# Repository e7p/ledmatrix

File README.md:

ledmatrix
=========

We got a couple of LED matrices in our Hackerspace /dev/tal in Wuppertal. Here there is held code and other useful things for them.

Important info: The Fusebit for "JTAG" MUST be deactivated for usage of PORT C, which is used by default for serial data!

How to build
------------

To build the Firmware, just enter the directory "main" and type `make`. For flashing the firmware `make flash` can be used, or the main.hex file can be flashed using an arbitrary AVR flashing tool.

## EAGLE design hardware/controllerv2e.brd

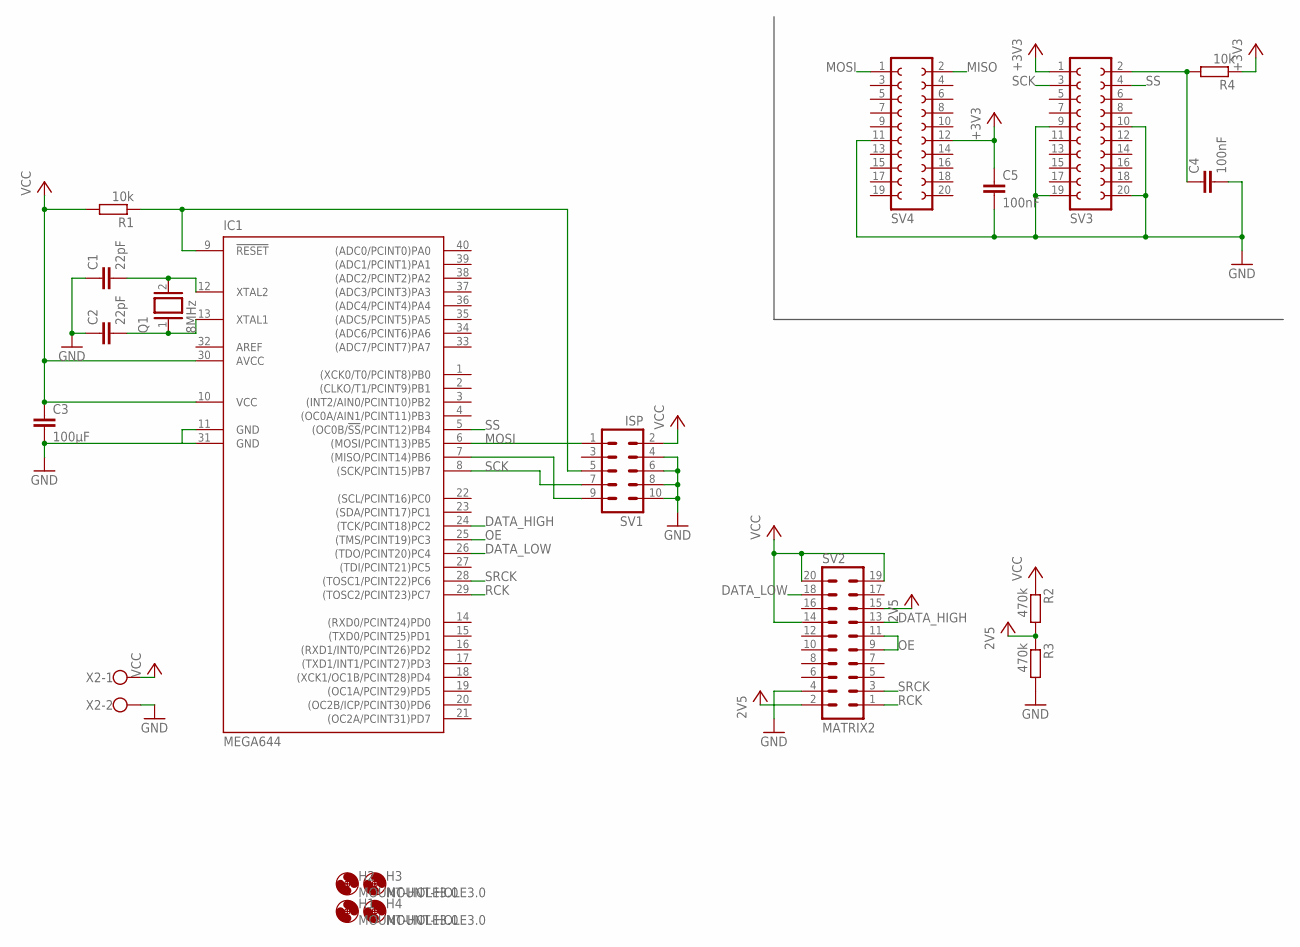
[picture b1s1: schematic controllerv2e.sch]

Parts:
C1, C2: 22pF; C050-024X044
C3: 100µF; C050-030X075
C4, C5: 100nF; C050-024X044
H1, H2, H3, H4: MOUNT-HOLE3.0; 3,0
IC1: MEGA644; DIL40
Q1: 8MHz; QS
R1, R4: 10k; 0207/10
R2, R3: 470k; 0207/10
SV1: ISP; ML10
SV2: MATRIX2; ML20
SV3, SV4: FE10-2
X2: GND; W237-102

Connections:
+3V3: C5.1, R2.2, R3.1, R4.1, SV2.2, SV2.15, SV3.1, SV4.12
AREF: IC1.32 (AREF)
DATA_HIGH: IC1.24 ((TCK/PCINT18)PC2), SV2.13
DATA_LOW: IC1.26 ((TDO/PCINT20)PC4), SV2.18
GND: C1.1, C2.1, C3.2, C4.2, C5.2, IC1.11 (GND), IC1.31 (GND), R3.2, SV1.4, SV1.6, SV1.8, SV1.10, SV2.4, SV3.9, SV3.10, SV3.19, SV3.20, SV4.11, X2.2
MISO: SV4.2
MOSI: IC1.6 ((MOSI/PCINT13)PB5), SV1.1, SV4.1
unnamed: C4.1, R4.2, SV3.2
unnamed: C2.2, IC1.13 (XTAL1), Q1.1
unnamed: C1.2, IC1.12 (XTAL2), Q1.2
unnamed: IC1.9 (!RESET), R1.1, SV1.5
unnamed: IC1.7 ((MISO/PCINT14)PB6), SV1.9
OE: IC1.25 ((TMS/PCINT19)PC3), SV2.9, SV2.11
RCK: IC1.29 ((TOSC2/PCINT23)PC7), SV2.1
SCK: IC1.8 ((SCK/PCINT15)PB7), SV1.7, SV3.3
SRCK: IC1.28 ((TOSC1/PCINT22)PC6), SV2.3
SS: IC1.5 ((OC0B/!SS!/PCINT12)PB4), SV3.4
VCC: C3.1, IC1.10 (VCC), IC1.30 (AVCC), R1.2, R2.1, SV1.2, SV2.14, SV2.19, SV2.20, X2.1

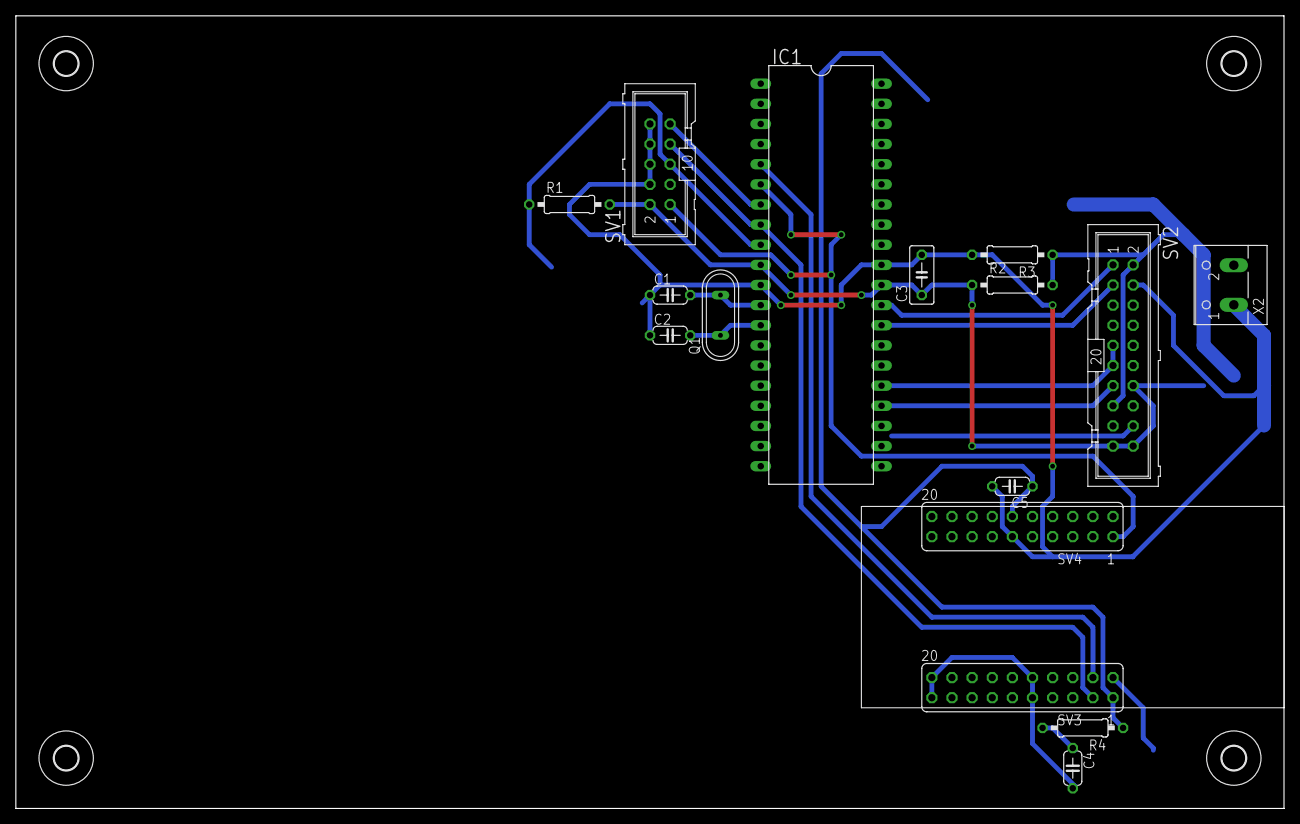
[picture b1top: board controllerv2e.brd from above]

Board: 2 copper layers, 160.0 x 100.0 mm, 20 parts (0 on the bottom side), 16 nets.

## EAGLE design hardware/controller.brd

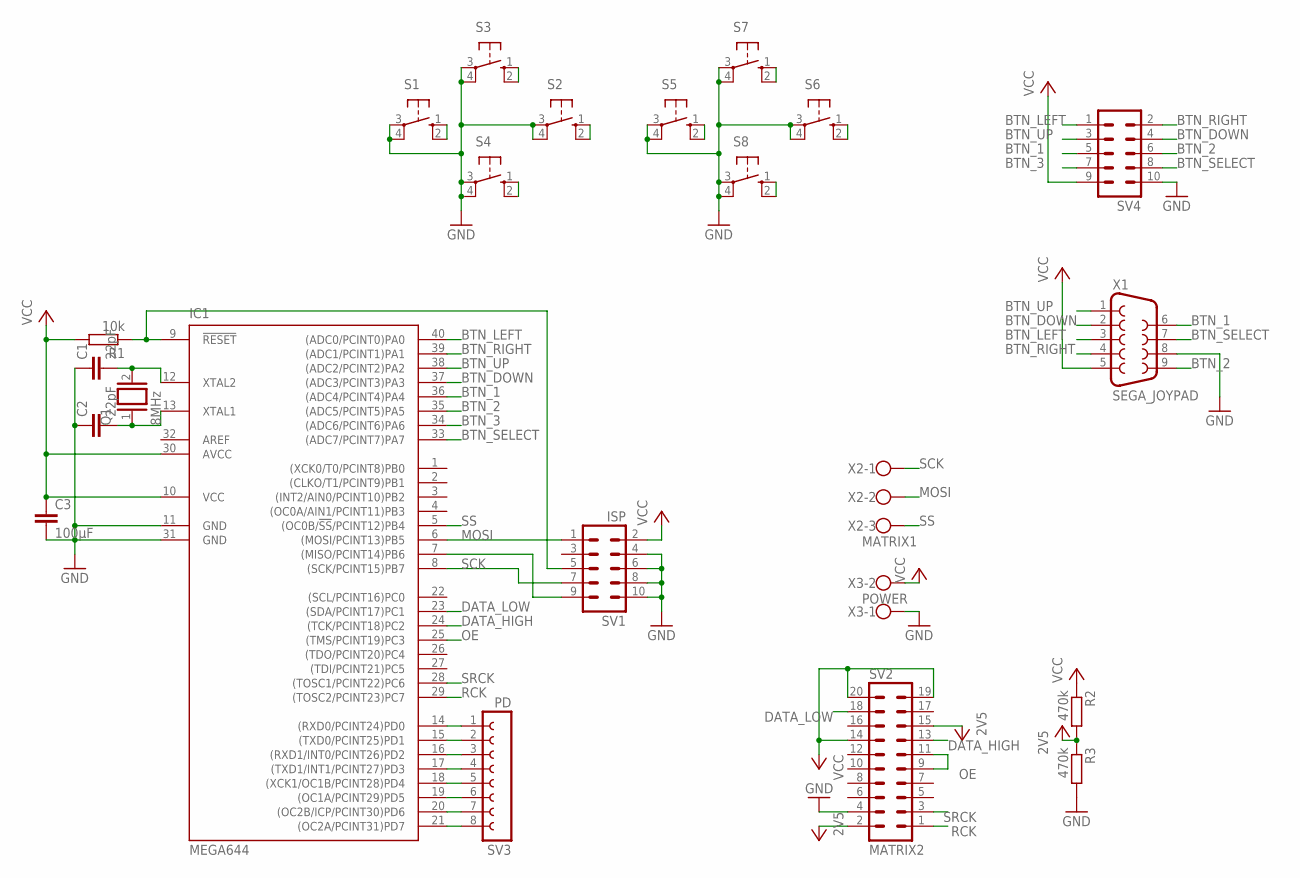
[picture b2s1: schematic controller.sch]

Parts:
C1, C2: 22pF; C050-024X044
C3: 100µF; C050-030X075
IC1: MEGA644; DIL40
Q1: 8MHz; QS
R1: 10k; 0207/10
R2, R3: 470k; 0207/10
S1, S5: 10-XX; B3F-10XX
S2, S3, S4, S6, S7, S8: 10-XX; B3F-10XX; MPN B3F-1000
SV1: ISP; ML10
SV2: MATRIX2; ML20
SV3: PD; FE08
SV4: ML10
X1: SEGA_JOYPAD; F09HP
X2: MATRIX1; W237-103
X3: POWER; W237-102

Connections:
+3V3: R2.2, R3.1, SV2.2, SV2.15
AREF: IC1.32 (AREF)
BTN_1: IC1.36 ((ADC4/PCINT4)PA4), S7.1 (S), S7.2 (S1), SV4.5, X1.6
BTN_2: IC1.35 ((ADC5/PCINT5)PA5), S5.1 (S), S5.2 (S1), SV4.6, X1.9
BTN_3: IC1.34 ((ADC6/PCINT6)PA6), S6.1 (S), S6.2 (S1), SV4.7
BTN_DOWN: IC1.37 ((ADC3/PCINT3)PA3), S4.1 (S), S4.2 (S1), SV4.4, X1.2
BTN_LEFT: IC1.40 ((ADC0/PCINT0)PA0), S1.1 (S), S1.2 (S1), SV4.1, X1.3
BTN_RIGHT: IC1.39 ((ADC1/PCINT1)PA1), S2.1 (S), S2.2 (S1), SV4.2, X1.4
BTN_SELECT: IC1.33 ((ADC7/PCINT7)PA7), S8.1 (S), S8.2 (S1), SV4.8, X1.7
BTN_UP: IC1.38 ((ADC2/PCINT2)PA2), S3.1 (S), S3.2 (S1), SV4.3, X1.1
DATA_HIGH: SV2.13
DATA_LOW: SV2.18
GND: C1.1, C2.1, C3.2, IC1.11 (GND), IC1.31 (GND), R3.2, S1.3, S1.4 (P1), S2.3, S2.4 (P1), S3.3, S3.4 (P1), S4.3, S4.4 (P1), S5.3, S5.4 (P1), S6.3, S6.4 (P1), S7.3, S7.4 (P1), S8.3, S8.4 (P1), SV1.4, SV1.6, SV1.8, SV1.10, SV2.4, SV4.10, X1.8, X3.1
MOSI: IC1.6 ((MOSI/PCINT13)PB5), SV1.1, X2.2
unnamed: C2.2, IC1.13 (XTAL1), Q1.1
unnamed: C1.2, IC1.12 (XTAL2), Q1.2
unnamed: IC1.9 (!RESET), R1.1, SV1.5
unnamed: IC1.14 ((RXD0/PCINT24)PD0), SV3.1
unnamed: IC1.7 ((MISO/PCINT14)PB6), SV1.9
unnamed: IC1.15 ((TXD0/PCINT25)PD1), SV3.2
unnamed: IC1.16 ((RXD1/INT0/PCINT26)PD2), SV3.3
unnamed: IC1.17 ((TXD1/INT1/PCINT27)PD3), SV3.4
unnamed: IC1.18 ((XCK1/OC1B/PCINT28)PD4), SV3.5
unnamed: IC1.19 ((OC1A/PCINT29)PD5), SV3.6
unnamed: IC1.20 ((OC2B/ICP/PCINT30)PD6), SV3.7
unnamed: IC1.21 ((OC2A/PCINT31)PD7), SV3.8
OE: SV2.9, SV2.11
RCK: IC1.29 ((TOSC2/PCINT23)PC7), SV2.1
SCK: IC1.8 ((SCK/PCINT15)PB7), SV1.7, X2.1
SRCK: IC1.28 ((TOSC1/PCINT22)PC6), SV2.3
SS: IC1.5 ((OC0B/!SS!/PCINT12)PB4), X2.3
VCC: C3.1, IC1.10 (VCC), IC1.30 (AVCC), R1.2, R2.1, SV1.2, SV2.14, SV2.19, SV2.20, SV4.9, X1.5, X3.2

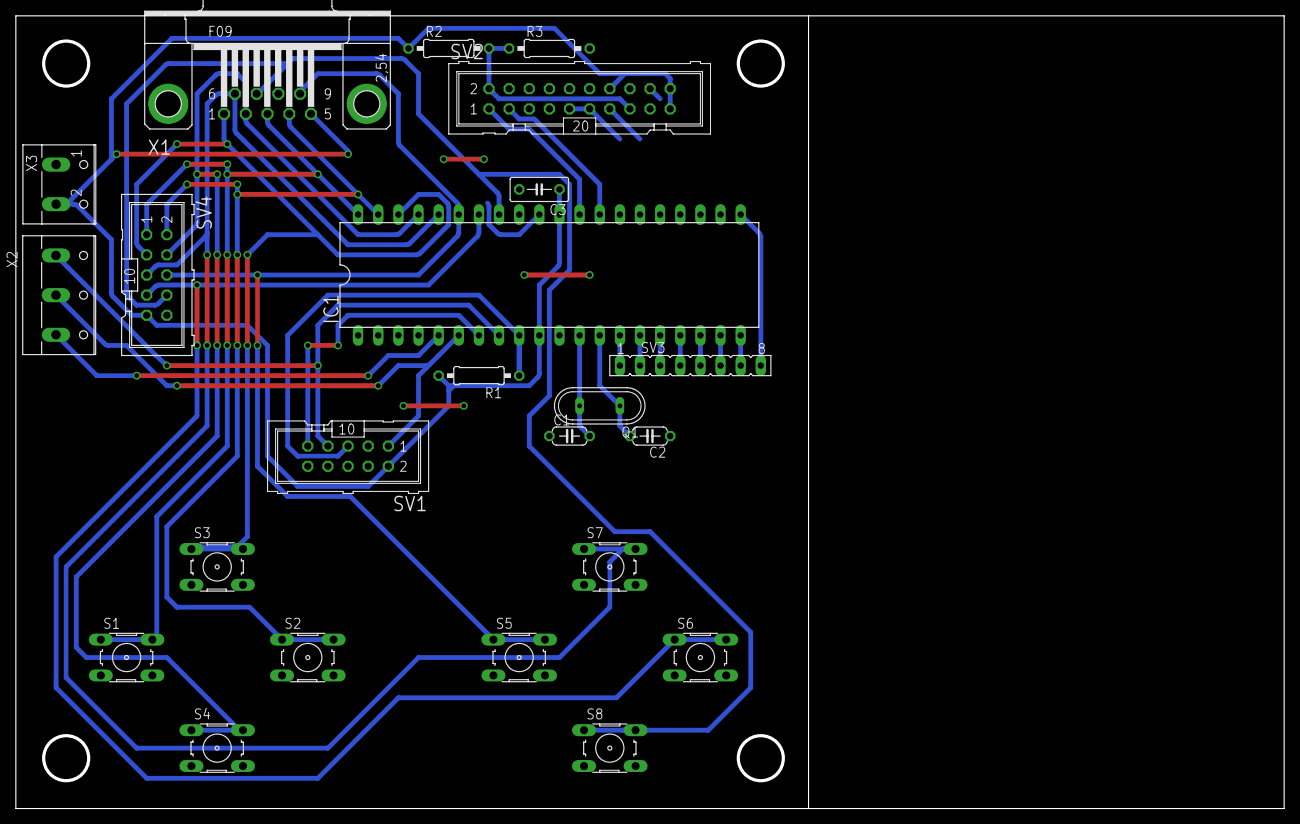
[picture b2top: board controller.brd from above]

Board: 2 copper layers, 160.0 x 100.0 mm, 23 parts (0 on the bottom side), 29 nets.

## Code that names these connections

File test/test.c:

/* Test for LED-Matrix 2
 * Code by Endres */
#define F_CPU 8000000UL
#include <avr/io.h>

#define DATA_LOW PC4
#define DATA_HIGH PC2
#define OE PC3
#define SRCK PC6
#define RCK PC7

#define PANELS 5
#define PANELDATA_SIZE (80*PANELS)

uint8_t panelData[PANELDATA_SIZE];

void clear() {
  for(uint8_t i = 0; i < PANELDATA_SIZE; i++) {
    panelData[i] = 0x00;
  }
}

void setPixel(uint8_t x, uint8_t y, uint8_t value) {
  if (value)
    panelData[2*x+y/8] |= 1 << (y % 8);
  else
    panelData[2*x+y/8] &= ~(1 << (y % 8));
}

void setRow(uint8_t x, uint8_t y, uint8_t value) {
  panelData[2*x+y] = value;
}

uint8_t getPixel(int x, int y) {
  return panelData[2*x+y/8] & (1 << (y % 8));
}

void screen_off() {
  PORTC &= ~(1<<OE);
}

void screen_on() {
  PORTC |= (1<<OE);
}

void shiftPixelData(uint8_t data) {
  for(int i = 0; i < PANELDATA_SIZE; i++) {
    uint8_t value_high = data; //panelData[i];
    uint8_t value_low = data; //panelData[++i];
    for(int j = 0; j < 8; j++) {
      PORTC &= ~((1<<DATA_LOW)|(1<<DATA_HIGH));
      PORTC |= ((value_low&1)<<DATA_LOW)|((value_high&1)<<DATA_HIGH);
      value_low = value_low >> 1;
      value_high = value_high >> 1;
      PORTC |= (1<<SRCK);
      PORTC &= ~(1<<SRCK);
    }
  }
  PORTC |= (1<<RCK);
  PORTC &= ~(1<<RCK);
}

void setup() {
  DDRC |= (1<<DATA_LOW)|(1<<DATA_HIGH)|(1<<OE)|(1<<SRCK)|(1<<RCK);
  screen_on();
}

void loop() {
  shiftPixelData(0xff);
}

int main() {
  setup();
  while(1) loop();
}

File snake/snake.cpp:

/* Snake Game for LED-Matrix "blinkofant"
 * Code by Endres, based on code by wizard23 */
#define F_CPU 8000000UL
#include <avr/io.h>
#include <avr/interrupt.h>
#include <util/delay.h>

#define CLEAR_PANEL_PIN PB4
// atmega pin #5 <-> panel pin #10

#define DATA_PIN PB5
// atmega pin #6 <-> panel pin #8

#define CLOCK_PIN PB7
// atmega pin #8 <-> panel pin #4 

#define LEFT_PIN PA0
#define RIGHT_PIN PA1

#define PANELS 1
#define PANELDATA_SIZE (10*PANELS)

#define DIR_RIGHT 0
#define DIR_BOTTOM 1
#define DIR_LEFT 2
#define DIR_TOP 3

uint8_t panelData[PANELDATA_SIZE];

uint8_t snakePos[PANELS*8*9][2];
uint8_t foodPos[2];
uint8_t snakeLength;
uint8_t snakeDir;

uint8_t buttonValue;
uint8_t buttonStatus;

uint8_t gameTick;

uint16_t random;

uint8_t cnt;
uint8_t bl;

void clear() {
  for(uint8_t i = 0; i < PANELDATA_SIZE; i++) {
    panelData[i] = 0;
  }
}

void setPixel(uint8_t x, uint8_t y, uint8_t value) {
  uint8_t index = (y+1) + x*10; // y+1 because 1st bit controls blinking
  uint8_t byteNum = index >> 3; // division by 8
  uint8_t bitNum = index & 0x7; // remainder at division by 8

  if (value)
    panelData[byteNum] |= 1 << bitNum;
  else
    panelData[byteNum] &= ~(1 << bitNum);
}

uint8_t getPixel(int x, int y) {
  uint8_t index = (y+1) + x*10; // See above
  uint8_t byteNum = index >> 3;
  uint8_t bitNum = index & 0x7;
  return panelData[index >> 3] & (1 << index & 0x7);
}

void togglePixel(int x, int y) {
  uint8_t index = (y+1) + x*10; // See above
  uint8_t byteNum = index >> 3;
  uint8_t bitNum = index & 0x7;
  panelData[byteNum] ^= 1 << bitNum;
}

void screen_off() {
  PORTB &= ~(1<<CLEAR_PANEL_PIN);
}

void screen_on() {
  PORTB |= (1<<CLEAR_PANEL_PIN);
}

bool inSnake(uint8_t x, uint8_t y) {
  for(uint8_t i = 0; i < snakeLength; i++) {
    if(snakePos[i][0] == x && snakePos[i][1] == y)
      return true;
  }
  return false;
}

void newFood() {
  do {
    foodPos[0] = random % 8;
    foodPos[1] = random % 9;
    random++;
  } while(inSnake(foodPos[0], foodPos[1]));
}

void shiftPixelData() {
  screen_off(); // needed?
  
  for(int i = 0; i < PANELDATA_SIZE; i++) {
    uint8_t value = panelData[i];
    
    SPDR = panelData[i];
    while(!(SPSR & (1<<SPIF)));
  }
  
  screen_on(); // needed?
}

#define SPI_MODE_MASK 0x0C  // CPOL = bit 3, CPHA = bit 2 on SPCR
#define SPI_MODE0 0x00
#define SPI_CLOCK_MASK 0x03  // SPR1 = bit 1, SPR0 = bit 0 on SPCR
#define SPI_CLOCK_DIV128 0x03
#define SPI_2XCLOCK_MASK 0x01  // SPI2X = bit 0 on SPSR

void setup() {
  // Initialize serial connection to matrix
  PORTB |= (1<<CLEAR_PANEL_PIN);
  DDRB |= (1<<CLEAR_PANEL_PIN)|(1<<DATA_PIN)|(1<<CLOCK_PIN);
  SPCR |= _BV(MSTR);
  SPCR |= _BV(SPE);
  SPCR |= _BV(DORD);
  SPCR = (SPCR & ~SPI_MODE_MASK) | SPI_MODE0;
  SPCR = (SPCR & ~SPI_CLOCK_MASK) | (SPI_CLOCK_DIV128 & SPI_CLOCK_MASK);
  SPSR = (SPSR & ~SPI_2XCLOCK_MASK) |
    ((SPI_CLOCK_DIV128 >> 2) & SPI_2XCLOCK_MASK);

  // Initialize Timers
  // 8-bit Timer 0 at 8.16ms
  TCCR0B |= (1<<CS02); // Prescaler 256
  // 16-bit Timer 1 at 524.28ms
  TCCR1B = (1<<CS00) | (1<<CS01); // Prescaler 64

  // Interrupts
  TIMSK0 |= (1<<TOIE0);
  TIMSK1 |= (1<<TOIE1);
  sei();

  // Initialize Snake
  snakeLength = 5;
  snakeDir = DIR_RIGHT;

  DDRA &= ~((1<<LEFT_PIN)|(1<<RIGHT_PIN));
  PORTA |= (1<<LEFT_PIN)|(1<<RIGHT_PIN);

  for(int x = 0; x < 8*PANELS; x++) {
    for(int y = 0; y < 9; y++) {
      if(y < 1 && x < snakeLength) {
        snakePos[x][0] = x;
        setPixel(x, y, 1);
      }
    }
  }
  
  newFood();
}

void shiftSnake() {
  for(int i = 0; i <= snakeLength; i++) {
    snakePos[i][0] = snakePos[i+1][0];
    snakePos[i][1] = snakePos[i+1][1];
  }
}

void snakeLeft() {
  snakeDir = (snakeDir + 3) % 4;
}

void snakeRight() {
  snakeDir = (snakeDir + 1) % 4;
}

void loop() {
  if(gameTick > 0) {
    if(buttonValue & (1<<LEFT_PIN)) snakeLeft();
    if(buttonValue & (1<<RIGHT_PIN)) snakeRight();
    buttonValue &= ~((1<<LEFT_PIN) | (1<<RIGHT_PIN));

    snakePos[snakeLength][0] = snakePos[snakeLength-1][0];
    snakePos[snakeLength][1] = snakePos[snakeLength-1][1];
    if(snakeDir == DIR_LEFT) {
      snakePos[snakeLength][0] = snakePos[snakeLength-1][0] - 1;
      if(snakePos[snakeLength][0] == 255) snakePos[snakeLength][0] = 7;
    } else if(snakeDir == DIR_RIGHT) {
      snakePos[snakeLength][0] = snakePos[snakeLength-1][0] + 1;
      if(snakePos[snakeLength][0] >= 8) snakePos[snakeLength][0] = 0;
    } else if(snakeDir == DIR_TOP) {
      snakePos[snakeLength][1] = snakePos[snakeLength-1][1] - 1;
      if(snakePos[snakeLength][1] == 255) snakePos[snakeLength][1] = 8;
    } else { // BOTTOM
      snakePos[snakeLength][1] = snakePos[snakeLength-1][1] + 1;
      if(snakePos[snakeLength][1] >= 9) snakePos[snakeLength][1] = 0;
    }
    
    if(snakePos[snakeLength][0] == foodPos[0] &&
      snakePos[snakeLength][1] == foodPos[1]) {
      snakeLength++;
      newFood();
    } else if(getPixel(snakePos[snakeLength][0], snakePos[snakeLength][1])) {
      // Game over
      //setPixel(0, 0, 1);
    } else {
      //setPixel(snakePos[0][0], snakePos[0][1], 0);
      //setPixel(snakePos[snakeLength][0], snakePos[snakeLength][1], 1);
      shiftSnake();
    }
    // draw Snake
    clear();
    for(uint8_t i = 0; i < snakeLength; i++) {
      setPixel(snakePos[i][0], snakePos[i][1], 1);
    }
    shiftPixelData();
    
    gameTick--;
  }
  if(cnt == 3) {
    setPixel(foodPos[0], foodPos[1], bl % 2);
    bl++;
    shiftPixelData();
    cnt = 0;
  }
  random++;
}

ISR(TIMER0_OVF_vect) {
  // Button timer (including simple debounce)
  buttonValue |= PINA & ~buttonStatus | buttonValue;
  buttonStatus = PINA | buttonStatus & buttonValue;
  cnt++;
}

ISR(TIMER1_OVF_vect) {
  // Game timer
  gameTick++;
}

int main() {
  setup();
  while(1) loop();
}

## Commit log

2013-02-02 Initial files
2013-02-03 Adding timers and status LEDs. The Input does not work as expected
2013-02-03 Supporting Assembler option
2013-02-08 Hardware and some fixes, but also more inefficient snake drawing
2013-02-08 Minor fix in gitignore
2013-02-09 New Marquee program. Does not scroll for now, but shows the letters one after each other.
2013-02-15 Marquee finished, only one bug left there: Last and first character ist not working very well.
2013-02-16 Updated Hardware
2013-03-08 Big text marquee and slight hardware modification
2013-03-09 new tetris-demo
2013-03-10 Completed Font to ASCII
2013-03-12 Fix in 'J'
2013-03-14 Introducing main application and web frontend
2013-03-14 development documentation
2013-03-14 updated uint16 data orientation
2013-03-14 clean up
2013-03-17 marquee2 set to 5 displays, new makefile strategy in test
2013-03-17 New makefile strategy
2013-03-20 Adding avrsim ledmatrix board.
2013-03-20 gitignore fix
2013-05-17 Update to current state of development
2013-05-17 New files to current state of development
2013-05-17 Tetris and needful things
2013-06-08 Tetris fixes
2013-06-15 Adding libraries and net_pong
2013-06-22 Fixing font library, working on network
2013-07-13 Network demo "nothing" works for now, but lib with underscore should be fixed
2013-07-13 net test working, no more net "nothing"
2013-07-13 Test 2 for LEDMatrix 2
2013-07-14 Code cleanup and net_time should work now!
2013-07-14 DST fix
2013-07-24 Net Time works now. font.c not really sure if it works like this.
2013-09-06 Adding DickesG and bugfix for timelib
2013-10-11 Sorting files, adding net_twitter
2013-10-12 new main program. needs slightly better module configuration through Makefiles
2013-10-18 Extending main app
2013-11-22 Message and command handling in main app
2013-12-21 Hotnews, Uptime, small changes in net_time
2014-03-31 Added labor font (until now only letters a,b,d,l,o,r,s)
2014-12-28 Langer Tisch commit von damals
2015-01-09 congress version
2015-01-09 new uptime module
2015-09-26 Pacman animation added
2015-10-30 added license, print version of the hardware, updated readme and modified NTP IP
2018-03-02 changed IP addresses for NTP and telnet
